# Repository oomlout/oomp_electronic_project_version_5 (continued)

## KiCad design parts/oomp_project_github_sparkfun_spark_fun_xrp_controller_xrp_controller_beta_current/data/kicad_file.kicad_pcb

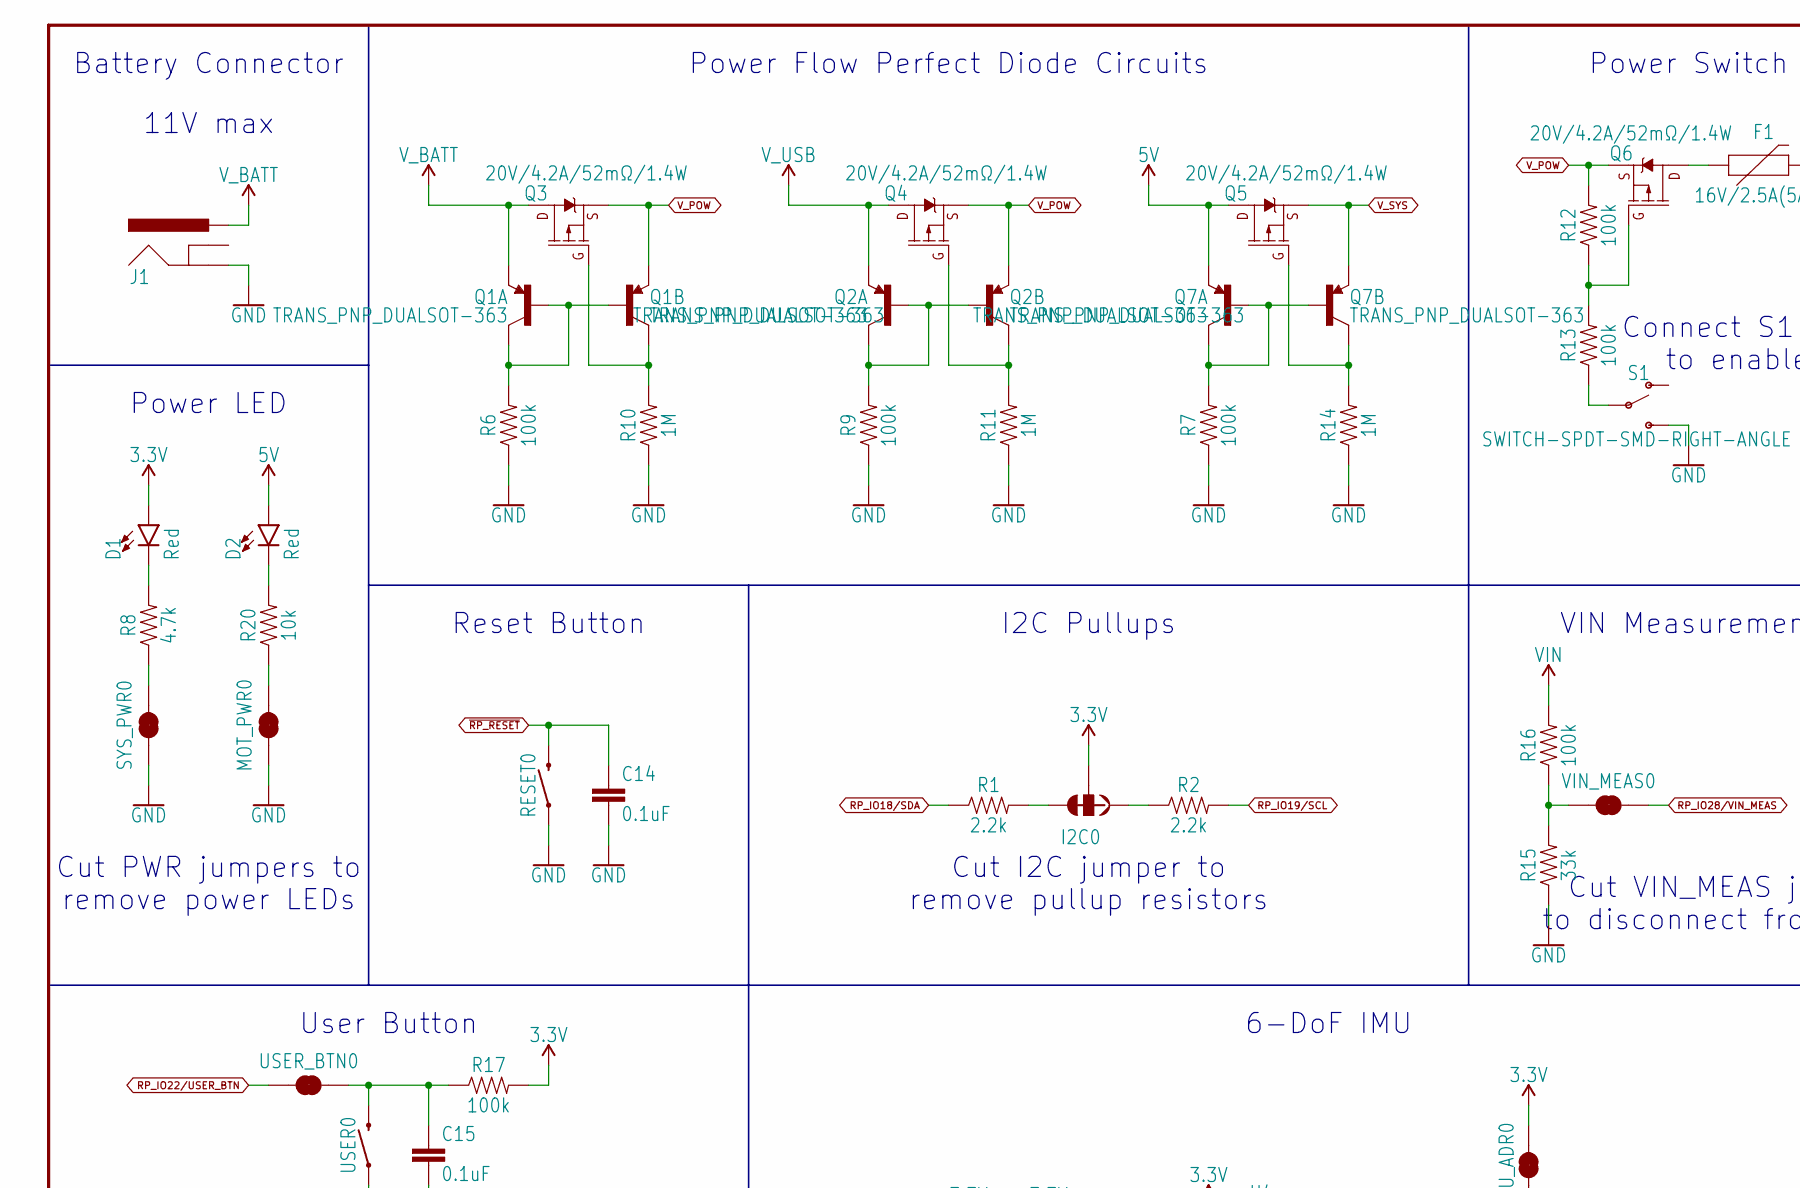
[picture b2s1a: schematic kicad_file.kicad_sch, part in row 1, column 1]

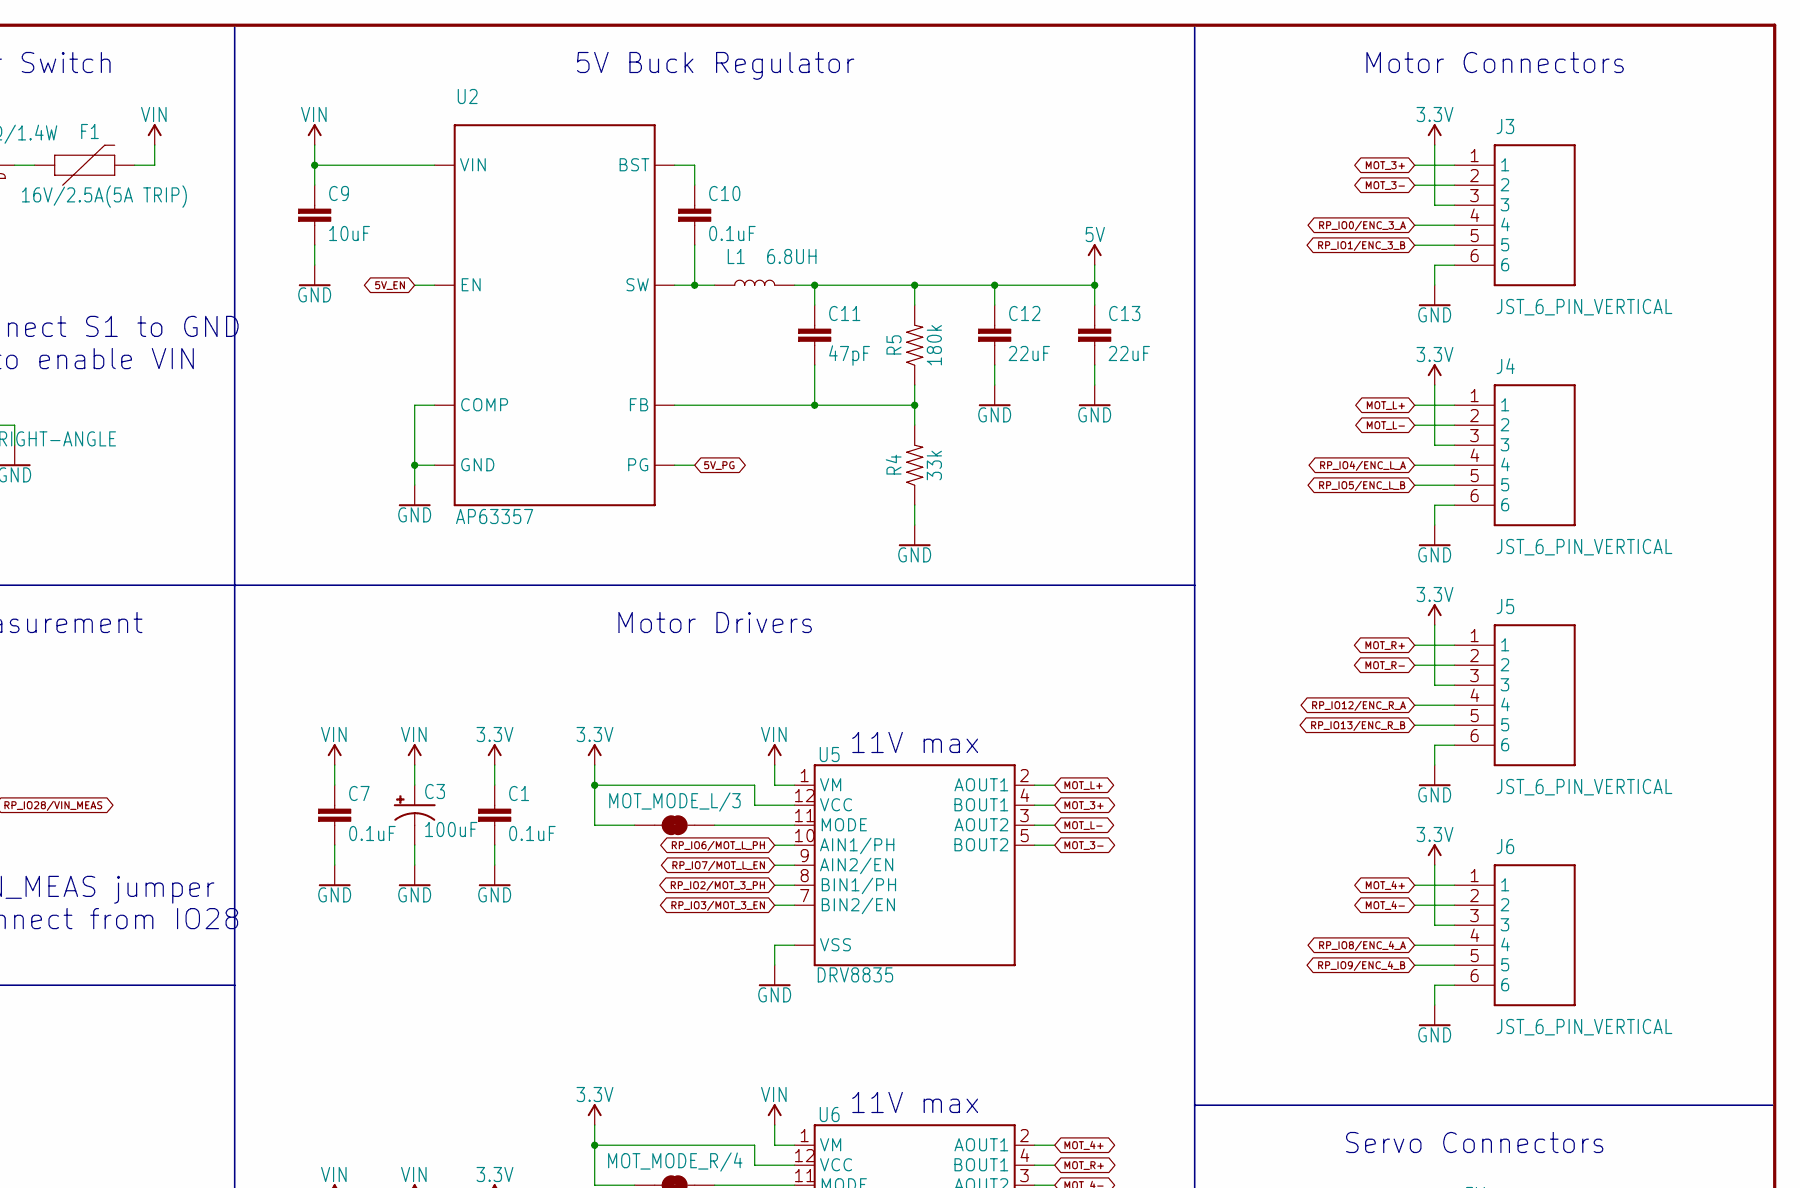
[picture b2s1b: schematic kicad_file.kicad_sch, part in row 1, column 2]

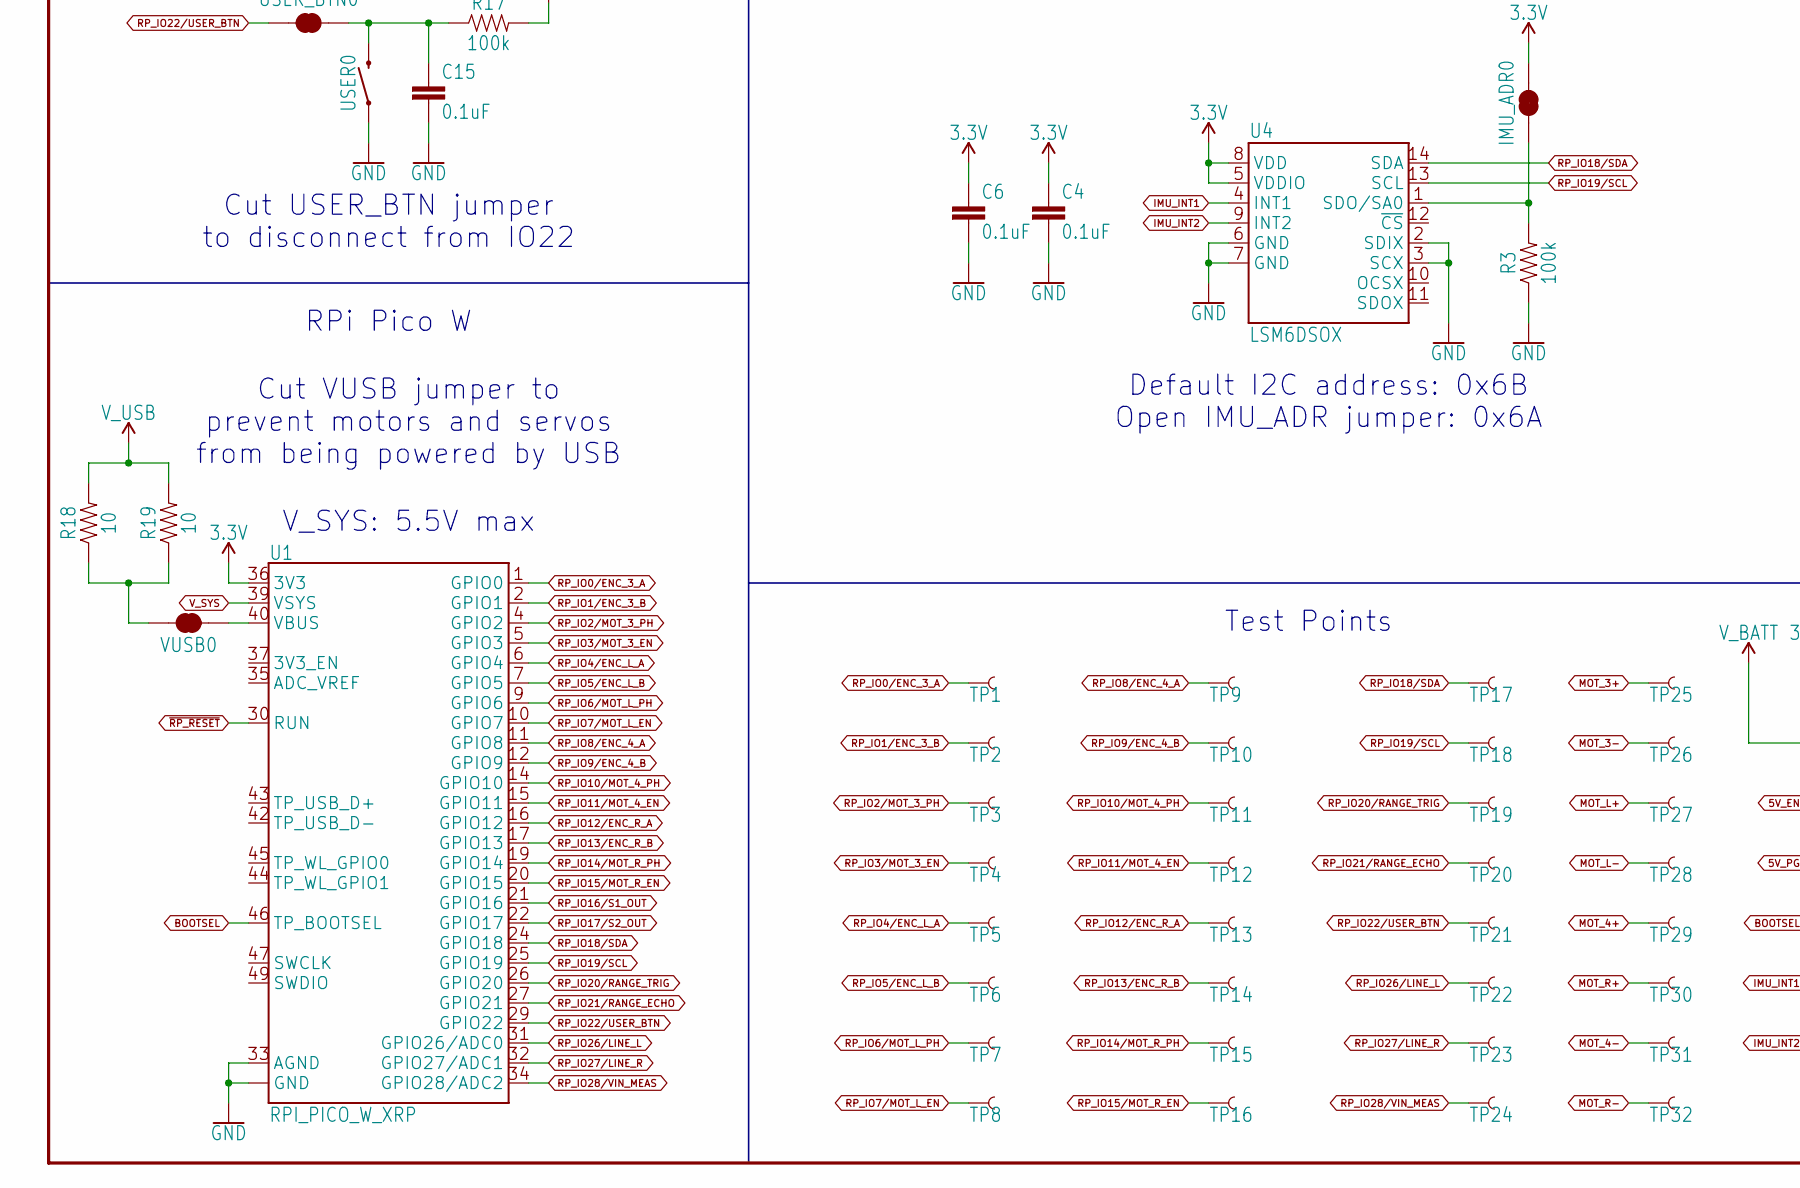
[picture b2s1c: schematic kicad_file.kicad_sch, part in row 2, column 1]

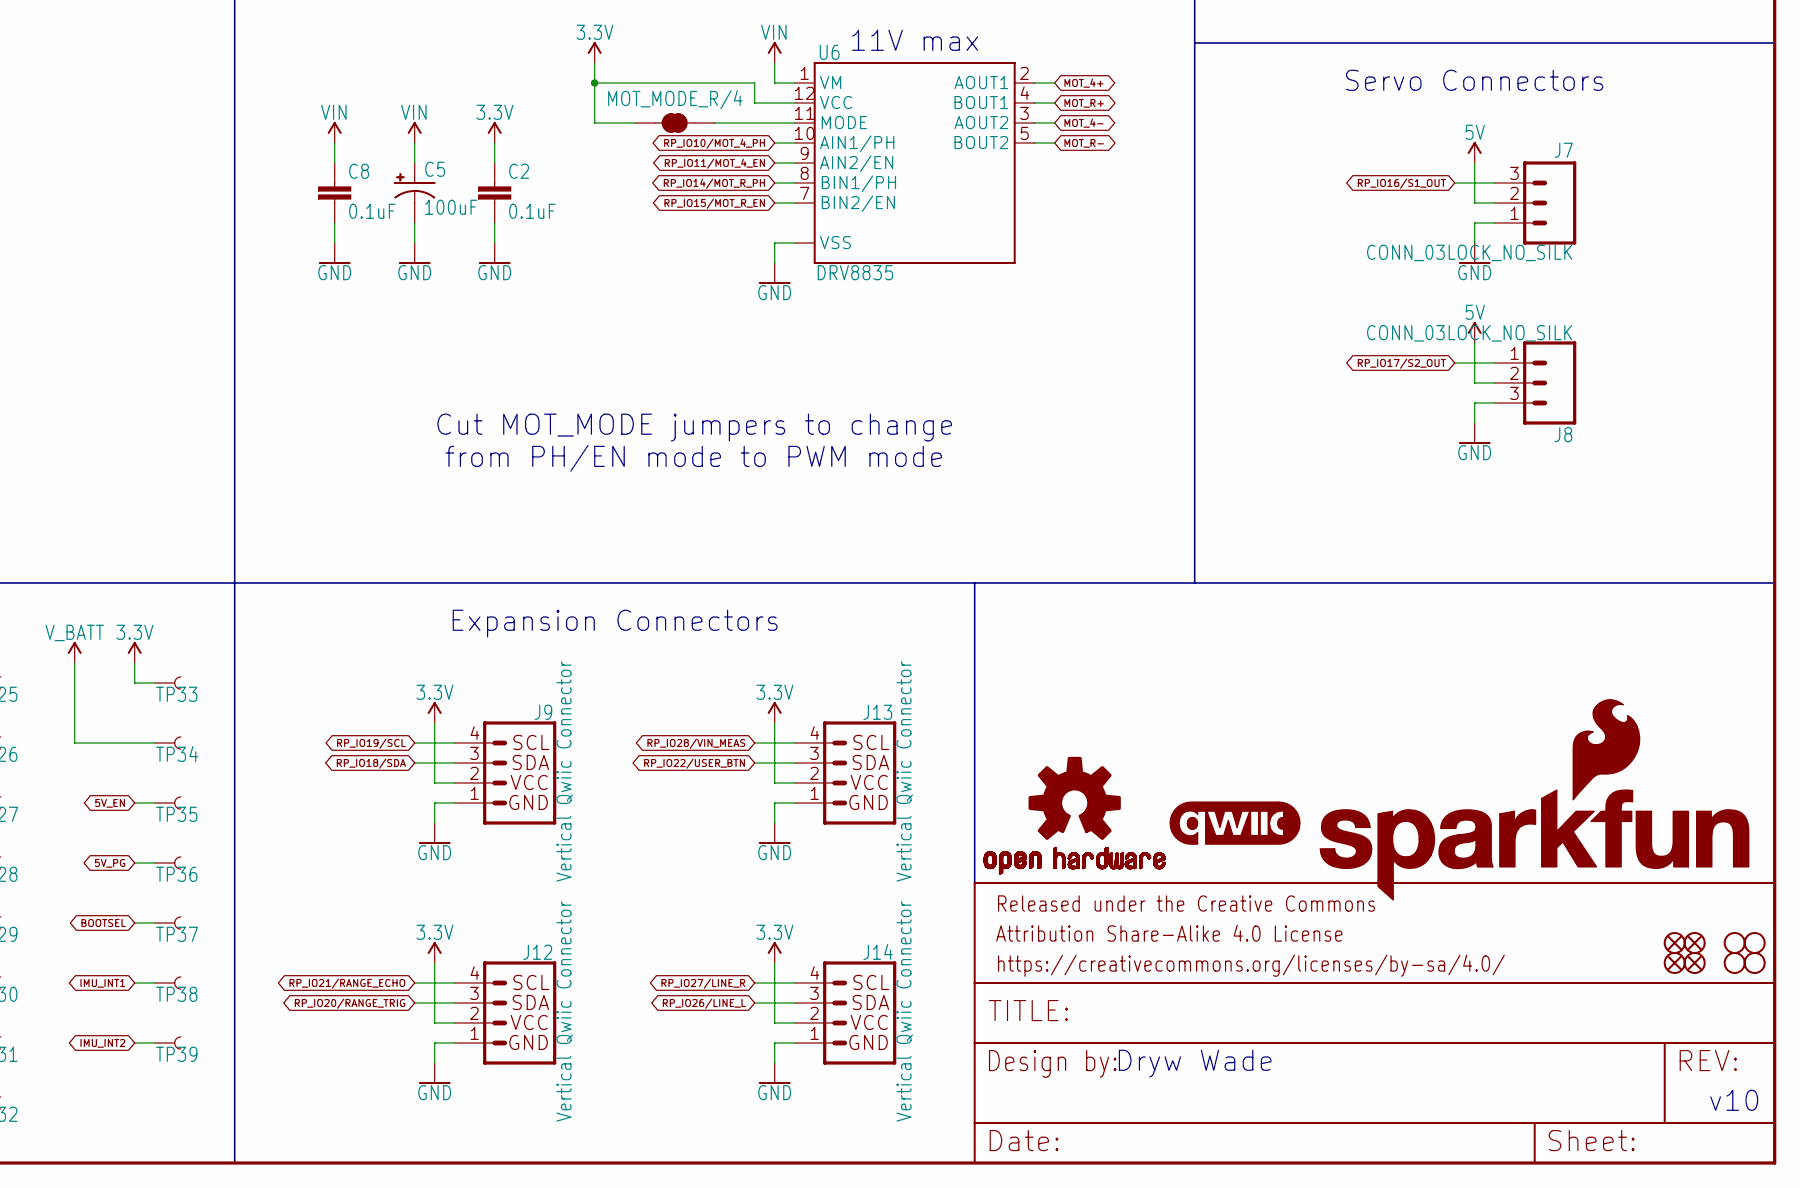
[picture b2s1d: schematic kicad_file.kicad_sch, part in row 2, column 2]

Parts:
C1, C2, C4, C6, C7, C8, C10, C14, C15: 0.1uF; 0603
C3, C5: 100uF; PANASONIC_D
C9: 10uF; 0805
C11: 47pF; 0603
C12, C13: 22uF; 0805
D1, D2: Red; LED-0603
F1: 16V/2.5A(5A TRIP); 1812
FD1, FD2, FD3, FD4: FIDUCIAL1X2; FIDUCIAL-1X2
FRAME1: FRAME-LEDGER; CREATIVE_COMMONS
H1, H2, H3, H4: STAND-OFF
I2C0: JUMPER-SMT_3_2-NC_TRACE_SILK; SMT-JUMPER_3_2-NC_TRACE_SILK
IMU_ADR0: JUMPER-SMT_2_NC_TRACE_SILK; SMT-JUMPER_2_NC_TRACE_SILK
J1: POWER_JACKPOWER_JACK_SLOT; POWER_JACK_PTH_SLOT
J3, J4, J5, J6: JST_6_PIN_VERTICAL; JST-6-SMD-VERT-1.0MM
J7, J8: CONN_03LOCK_NO_SILK; 1X03_LOCK_NO_SILK
J9, J12, J13, J14: Vertical Qwiic Connector; JST04_1MM_VERT
L1: 6.8UH; 07A7_6U8H
LOGO1: OSHW-LOGOS; OSHW-LOGO-S
LOGO3: SFE_LOGO_NAME_FLAME.3_INCH; SFE_LOGO_NAME_FLAME_.3
MOT_MODE_L/3: JUMPER-SMT_2_NC_TRACE_SILK; SMT-JUMPER_2_NC_TRACE_SILK
MOT_MODE_R/4: JUMPER-SMT_2_NC_TRACE_SILK; SMT-JUMPER_2_NC_TRACE_SILK
MOT_PWR0: JUMPER-SMT_2_NC_TRACE_SILK; SMT-JUMPER_2_NC_TRACE_SILK
Q1, Q2, Q7: TRANS_PNP_DUALSOT-363; SOT363_PHILIPS
Q3, Q4, Q5, Q6: 20V/4.2A/52mΩ/1.4W; SOT23-3
R1, R2: 2.2k; 0603
R3, R6, R7, R9, R12, R13, R16, R17: 100k; 0603
R4, R15: 33k; 0603
R5: 180k; 0603
R8: 4.7k; 0603
R10, R11, R14: 1M; 0603
R18, R19: 10; 1206
R20: 10k; 0603
RESET0: MOMENTARY-SWITCH-SPST-SMD-4.6X2.8MM; TACTILE_SWITCH_SMD_4.6X2.8MM
S1: SWITCH-SPDT-SMD-RIGHT-ANGLE; SWITCH_SPST_SMD_A
SYS_PWR0: JUMPER-SMT_2_NC_TRACE_SILK; SMT-JUMPER_2_NC_TRACE_SILK
TP1, TP2, TP3, TP4, TP5, TP6, TP7, TP8, TP9, TP10, TP11, TP12, TP13, TP14, TP15, TP16, TP17, TP18, TP19, TP20, TP21, TP22, TP23, TP24, TP25, TP26, TP27, TP28, TP29, TP30, TP31, TP32, TP33, TP34, TP35, TP36, TP37, TP38, TP39: TEST-POINT3X5; PAD.03X.05
U1: RPI_PICO_W_XRP; RPI_PICO_W
U2: AP63357; V-DFN3020-13
U4: LSM6DSOX; LGA14L
U5, U6: DRV8835; WSON-12
U$98: QWIIC_LOGO_5MM_INVERTED; QWIIC_5MM_INVERTED
USER0: MOMENTARY-SWITCH-SPST-SMD-4.6X2.8MM; TACTILE_SWITCH_SMD_4.6X2.8MM
USER_BTN0: JUMPER-SMT_2_NC_TRACE_SILK; SMT-JUMPER_2_NC_TRACE_SILK
VIN_MEAS0: JUMPER-SMT_2_NC_TRACE_SILK; SMT-JUMPER_2_NC_TRACE_SILK
VUSB0: JUMPER-SMT_2_NC_TRACE_SILK; SMT-JUMPER_2_NC_TRACE_SILK

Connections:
3.3V: C1.1, C2.1, C4.1, C6.1, D1.A, I2C0.2, IMU_ADR0.2, J3.3, J4.3, J5.3, J6.3, J9.2, J12.2, J13.2, J14.2, MOT_MODE_L/3.2, MOT_MODE_R/4.2, R17.2, TP33.1, U1.36 (3V3), U4.5 (VDDIO), U4.8 (VDD), U5.12 (VCC), U6.12 (VCC)
5V: C11.1, C12.1, C13.1, D2.A, J7.2, J8.2, L1.P$2 (2), Q5.3 (D), Q7.1 (E), R5.2
5V_EN: TP35.1, U2.P$2 (EN)
5V_PG: TP36.1, U2.P$5 (PG)
BOOTSEL: TP37.1, U1.46 (TP_BOOTSEL)
FB: C11.2, R4.2, R5.1, U2.P$3 (FB)
GND: C1.2, C2.2, C3.-, C4.2, C5.-, C6.2, C7.2, C8.2, C9.2, C12.2, C13.2, C14.2, C15.2, J1.GND, J3.6, J4.6, J5.6, J6.6, J7.1, J8.3, J9.1, J12.1, J13.1, J14.1, MOT_PWR0.1, R3.1, R4.1, R6.1, R7.1, R9.1, R10.1, R11.1, R14.1, R15.1, RESET0.1, RESET0.2 (1), S1.3 (S), SYS_PWR0.1, U1.3 (GND), U1.8 (GND), U1.13 (GND), U1.18 (GND), U1.23 (GND), U1.28 (GND), U1.33 (AGND), U1.38 (GND), U1.41 (GND), U1.48 (GND), U1.A (GND), U1.B (GND), U1.C (GND), U1.D (GND), U2.P$4 (COMP), U2.P$8 (GND), U4.2 (SDIX), U4.3 (SCX), U4.6 (GND), U4.7 (GND), U5.6 (VSS), U5.PAD (VSS), U6.6 (VSS), U6.PAD (VSS), USER0.1, USER0.2 (1)
IMU_INT1: TP38.1, U4.4 (INT1)
IMU_INT2: TP39.1, U4.9 (INT2)
MOT_3+: J3.1, TP25.1, U5.4 (BOUT1)
MOT_3-: J3.2, TP26.1, U5.5 (BOUT2)
MOT_4+: J6.1, TP29.1, U6.2 (AOUT1)
MOT_4-: J6.2, TP31.1, U6.3 (AOUT2)
MOT_L+: J4.1, TP27.1, U5.2 (AOUT1)
MOT_L-: J4.2, TP28.1, U5.3 (AOUT2)
MOT_R+: J5.1, TP30.1, U6.4 (BOUT1)
MOT_R-: J5.2, TP32.1, U6.5 (BOUT2)
unnamed: D1.C, R8.2
unnamed: IMU_ADR0.1, R3.2, U4.1 (SDO/SA0)
unnamed: I2C0.3, R1.2
unnamed: I2C0.1, R2.1
unnamed: C10.1, U2.P$6 (BST)
unnamed: Q1.2 (B), Q1.5 (B), Q1.6 (C), R6.2
unnamed: Q1.3 (C), Q3.1 (G), R10.2
unnamed: F1.1, Q6.3 (D)
unnamed: U1.40 (VBUS), VUSB0.2
unnamed: R8.1, SYS_PWR0.2
unnamed: Q2.2 (B), Q2.5 (B), Q2.6 (C), R9.2
unnamed: R15.2, R16.1, VIN_MEAS0.2
unnamed: MOT_MODE_L/3.1, U5.11 (MODE)
unnamed: MOT_MODE_R/4.1, U6.11 (MODE)
unnamed: Q6.1 (G), R12.1, R13.2
unnamed: Q2.3 (C), Q4.1 (G), R11.2
unnamed: C15.1, R17.1, USER0.3 (2), USER0.4 (2), USER_BTN0.1
unnamed: R18.1, R19.1, VUSB0.1
unnamed: Q7.2 (B), Q7.5 (B), Q7.6 (C), R7.2
unnamed: Q5.1 (G), Q7.3 (C), R14.2
unnamed: D2.C, R20.2
unnamed: MOT_PWR0.2, R20.1
RP_IO0/ENC_3_A: J3.4, TP1.1, U1.1 (GPIO0)
RP_IO1/ENC_3_B: J3.5, TP2.1, U1.2 (GPIO1)
RP_IO2/MOT_3_PH: TP3.1, U1.4 (GPIO2), U5.8 (BIN1/PH)
RP_IO3/MOT_3_EN: TP4.1, U1.5 (GPIO3), U5.7 (BIN2/EN)
RP_IO4/ENC_L_A: J4.4, TP5.1, U1.6 (GPIO4)
RP_IO5/ENC_L_B: J4.5, TP6.1, U1.7 (GPIO5)
RP_IO6/MOT_L_PH: TP7.1, U1.9 (GPIO6), U5.10 (AIN1/PH)
RP_IO7/MOT_L_EN: TP8.1, U1.10 (GPIO7), U5.9 (AIN2/EN)
RP_IO8/ENC_4_A: J6.4, TP9.1, U1.11 (GPIO8)
RP_IO9/ENC_4_B: J6.5, TP10.1, U1.12 (GPIO9)
RP_IO10/MOT_4_PH: TP11.1, U1.14 (GPIO10), U6.10 (AIN1/PH)
RP_IO11/MOT_4_EN: TP12.1, U1.15 (GPIO11), U6.9 (AIN2/EN)
RP_IO12/ENC_R_A: J5.4, TP13.1, U1.16 (GPIO12)
RP_IO13/ENC_R_B: J5.5, TP14.1, U1.17 (GPIO13)
RP_IO14/MOT_R_PH: TP15.1, U1.19 (GPIO14), U6.8 (BIN1/PH)
RP_IO15/MOT_R_EN: TP16.1, U1.20 (GPIO15), U6.7 (BIN2/EN)
RP_IO16/S1_OUT: J7.3, U1.21 (GPIO16)
RP_IO17/S2_OUT: J8.1, U1.22 (GPIO17)
RP_IO18/SDA: J9.3, R1.1, TP17.1, U1.24 (GPIO18), U4.14 (SDA)
RP_IO19/SCL: J9.4, R2.2, TP18.1, U1.25 (GPIO19), U4.13 (SCL)
RP_IO20/RANGE_TRIG: J12.3, TP19.1, U1.26 (GPIO20)
RP_IO21/RANGE_ECHO: J12.4, TP20.1, U1.27 (GPIO21)
RP_IO22/USER_BTN: J13.3, TP21.1, U1.29 (GPIO22), USER_BTN0.2
RP_IO26/LINE_L: J14.3, TP22.1, U1.31 (GPIO26/ADC0)
RP_IO27/LINE_R: J14.4, TP23.1, U1.32 (GPIO27/ADC1)
RP_IO28/VIN_MEAS: J13.4, TP24.1, U1.34 (GPIO28/ADC2), VIN_MEAS0.1
SW: C10.2, L1.P$1 (1), U2.P$7 (SW), U2.P$9 (SW)
VIN: C3.+, C5.+, C7.1, C8.1, C9.1, F1.2, R16.2, U2.P$1 (VIN), U5.1 (VM), U6.1 (VM)
V_BATT: J1.PWR, Q1.1 (E), Q3.3 (D), TP34.1
V_POW: Q1.4 (E), Q2.4 (E), Q3.2 (S), Q4.2 (S), Q6.2 (S), R12.2
V_SYS: Q5.2 (S), Q7.4 (E), U1.39 (VSYS)
V_USB: Q2.1 (E), Q4.3 (D), R18.2, R19.2
~POW_EN: R13.1, S1.2
~RP_RESET: C14.1, RESET0.3 (2), RESET0.4 (2), U1.30 (RUN)

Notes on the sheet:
Cut VUSB jumper to prevent motors and servos from being powered by USB
VIN Measurement
RPi Pico W
Servo Connectors
Cut PWR jumpers to remove power LEDs
Expansion Connectors
User Button
Reset Button
11V max~{}
Motor Drivers
Cut VIN_MEAS jumper to disconnect from IO28
Cut I2C jumper to remove pullup resistors
Cut USER_BTN jumper to disconnect from IO22
Power LED
6-DoF IMU
Default I2C address: 0x6B Open IMU_ADR jumper: 0x6A
5V Buck Regulator
Test Points
V_SYS: 5.5V max~{}
Cut MOT_MODE jumpers to change from PH/EN mode to PWM mode
I2C Pullups
Dryw Wade
v10
Power Switch
Power Flow Perfect Diode Circuits
Motor Connectors
Connect S1 to GND to enable VIN
Battery Connector

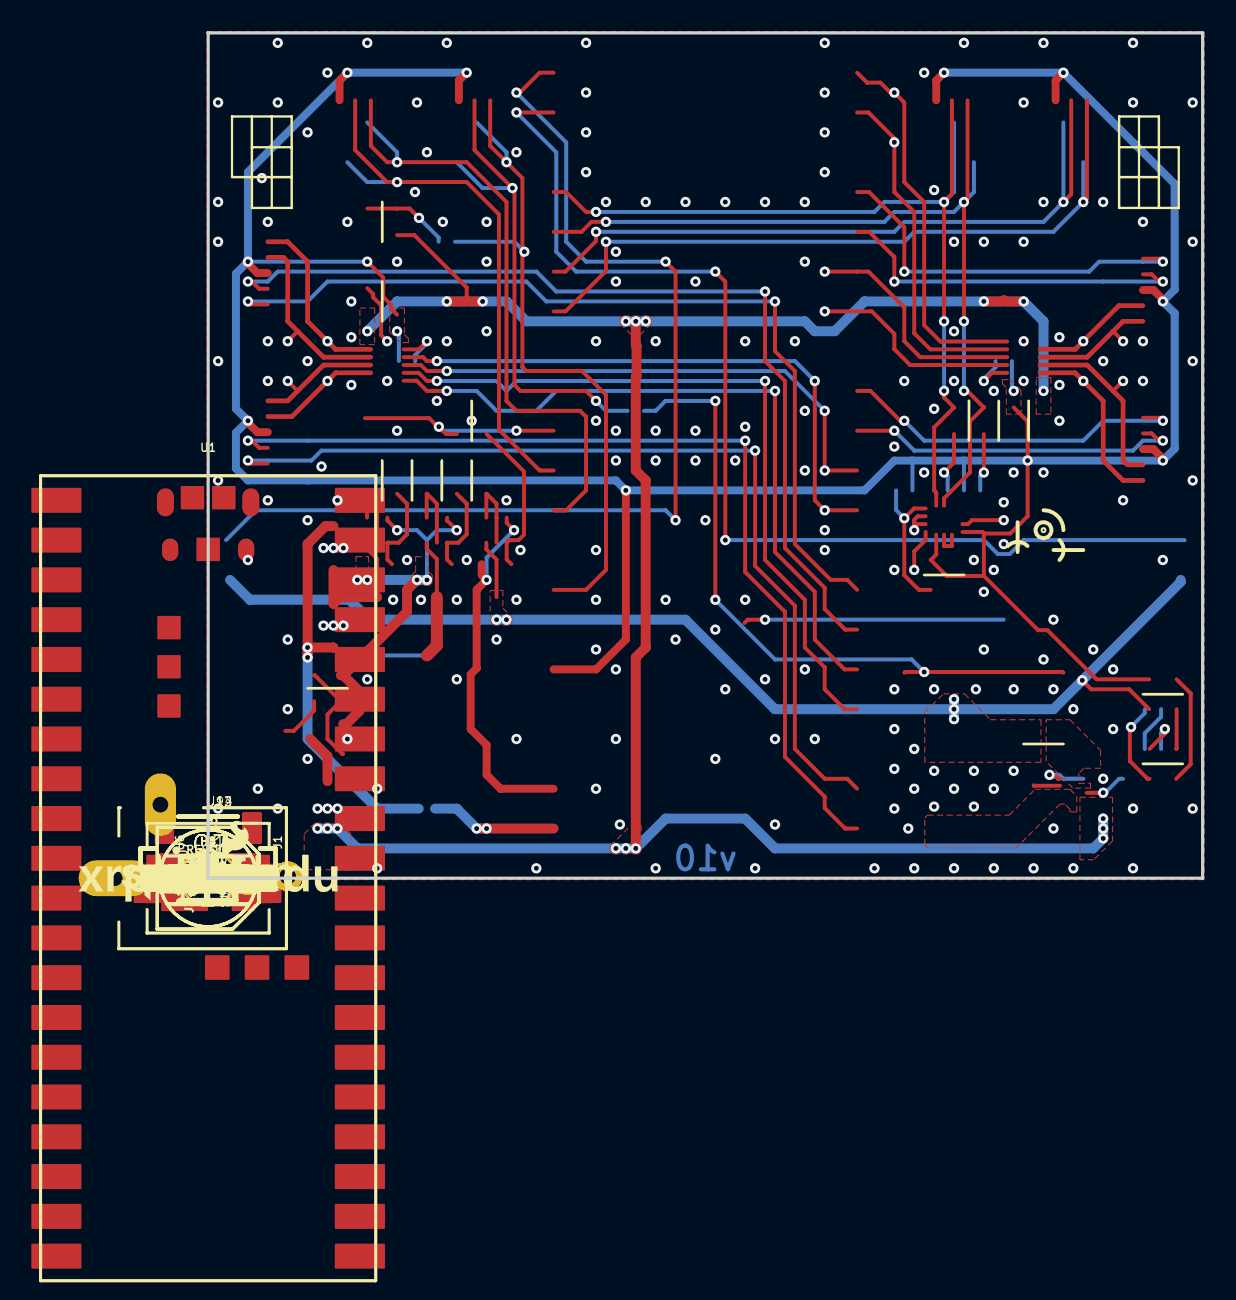
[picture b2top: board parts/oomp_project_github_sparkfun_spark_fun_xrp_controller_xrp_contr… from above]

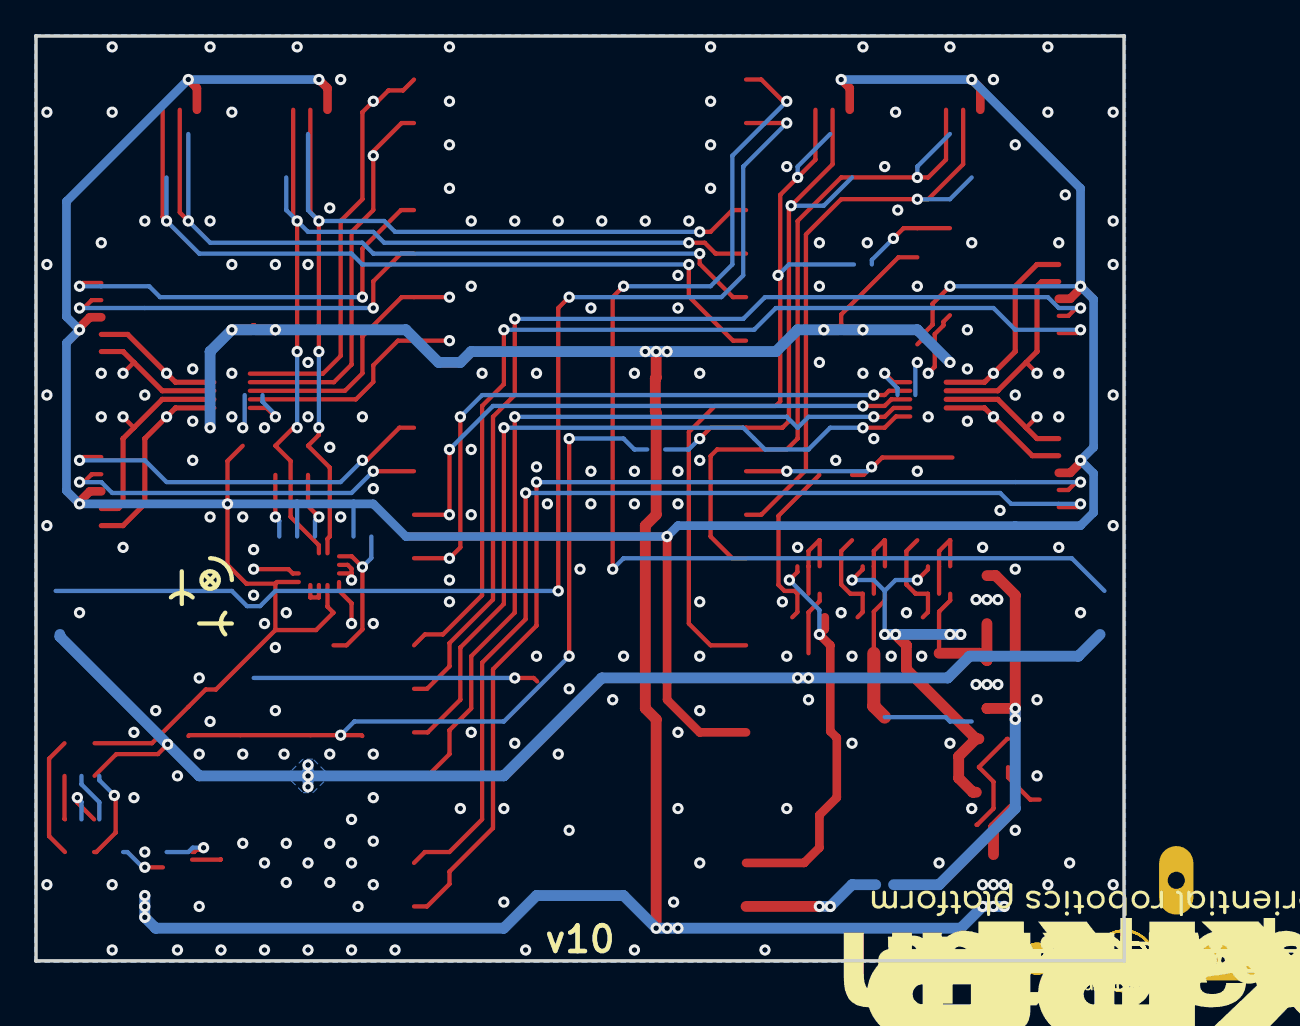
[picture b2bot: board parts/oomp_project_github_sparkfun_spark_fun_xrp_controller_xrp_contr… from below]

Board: 2 copper layers, 63.5 x 54.0 mm, 240 parts (76 on the bottom side), 73 nets.

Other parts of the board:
LOGO4: SFE_LOGO_NAME_FLAME.1_INCH; SFE_LOGO_NAME_FLAME_.1
U$1: #MOTOR_3#0
U$2: #SERVO_2#0
U$3: #11V_MAX###0
U$4, U$24, U$50, U$52, U$54: #GND#0
U$5: #POWER#0
U$6: PWR0
U$7: RESET0
U$8: #MOTOR_R#0
U$9: #MR##0
U$10: #MOTOR_L#0
U$11: #SERVO_1#0
U$12: #MOTOR_4#0
U$13: #VIN_MEAS#0
U$14: #MR##1
U$15, U$25, U$51, U$53: #3V3#0
U$16: #ML##0
U$17, U$33, U$41, U$43: #3V3#4
U$18: #M4##0
U$19: #M4##5
U$20: #IO0#0
U$21: #IO1#0
U$22: #IO5#0
U$23: #IO4#0
U$26: #GND_#0
U$27: #5V_#0
U$28: #IO8#0
U$29: #IO9#0
U$30, U$31, U$40, U$42, U$57: #GND#10
U$32: #ML##1
U$34: #IO12#0
U$35: #IO13#0
U$36: ORDERING_INSTRUCTIONS
U$37, U$117: #PH#0
U$38: #IO27#0
U$39: #IO28#0
U$44: #IO26#0
U$45: #IO22#0
U$46: #IO18#0
U$47: #IO19#0
U$48: #IO20#0
U$49: #IO21#0
U$55: #5V#0
U$56: #IO16#0
U$58: #IO17#0
U$59: #5V#18
U$60: #I2C#0
U$61: #IO16_#0
U$62: ON0
U$63: OFF0
U$64: #IMU_ADR#0
U$65, U$116: #EN#0
U$66: #MOT_MODE_L#3#0
U$67: SYS0
U$68: IO220
U$69: #RANGE#0
U$70: #MOT_MODE_R#4#0
U$71: MOT0
U$72: XRP_URL_3MM
U$73: #PWR#0
U$74: #LINE#0
U$75: #_GND#0
U$76: #_5V#0
U$77: #_IO17#0
U$78: POLARITY_MARKING_CENTER_POSITIVE#JPG
U$79, U$88: X0
U$80, U$89: Y0
U$81, U$90: Z0
U$82: #EXTRA#0
U$83: USER0
U$84: #USER_BTN#0
U$85: 0X6B0
U$86: 0X6A0
U$87: OPEN#0
U$91: CLOSED#0
U$92: XRP_FULL_LOGO
U$93: #VUSB#0
U$94: #M3##0
U$95: #MOT#0
U$96: #SYS#0
U$97: XRP_URL_5MM
U$99: #M3##4
U$100: #ML#0
U$101: #M3#0
U$102: 100
U$103: 110
U$104: 140
U$105: 150
U$106: #MR#0
U$107: #M4#0
U$108: 20
U$109: 30
U$110: 60
U$111: 70
U$114, U$115: MOTOR_IO0

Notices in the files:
parts/oomp_project_github_sparkfun_spark_fun_xrp_controller_xrp_controller_beta_current/data/kicad_file.kicad_sch:
Released under the Creative Commons
https://creativecommons.org/licenses/by-sa/4.0
parts and their libraries:
Released under the Creative Commons Attribution Share-Alike 4.0 License
